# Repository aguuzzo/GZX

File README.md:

# **Robot Seguidor de Líneas**

Este proyecto implementa un robot seguidor de líneas basado en un Arduino Nano, 6 sensores CNY70, motores Pololu y un driver de motores. El robot utiliza un algoritmo de control para seguir de forma eficiente una línea negra sobre un fondo blanco.

---

## **Características**

- **Sensores:** 6 sensores CNY70 para detección precisa de la línea.  
- **Controlador:** Arduino Nano para procesamiento y control.  
- **Motores:** Motores Pololu de corriente continua para el movimiento.  
- **Driver de Motores:** Permite controlar la dirección y velocidad de los motores.  
- **Algoritmo de Control:** Basado en control proporcional (P) o proporcional-derivativo (PD) para seguir la línea.

---

## **Componentes**

- **Microcontrolador:** Arduino Nano (ATmega328P).  
- **Sensores:** 6 sensores ópticos CNY70.  
- **Motores:** Motores Pololu con caja reductora.  
- **Driver de Motores:** L298N o TB6612FNG.  
- **Fuente de Alimentación:** Batería de 7.4V (para los motores) y regulador de 5V para el Arduino y sensores.  
- **Estructura:** Chasis con diseño ligero y estable.  

---

## **Conexiones**

### **Sensores CNY70**  
Conectados a las entradas analógicas del Arduino:  
- **A0, A1, A2, A3, A4, A5.**  

### **Driver de Motores**  
Pines del Arduino conectados al driver:  
- **ENA:** Pin 9 (Control de velocidad motor izquierdo).  
- **IN1, IN2:** Pines 7 y 6 (Control dirección motor izquierdo).  
- **ENB:** Pin 10 (Control de velocidad motor derecho).  
- **IN3, IN4:** Pines 5 y 4 (Control dirección motor derecho).  

---

## **Algoritmo Implementado**

1. Leer los valores de los sensores (valores analógicos).  
2. Convertir los valores a binarios según un umbral.  
3. Calcular la posición de la línea en relación con el centro de los sensores.  
4. Determinar el error y ajustar la velocidad de los motores mediante un controlador proporcional (P).  
5. Enviar comandos al driver para mover los motores.

---

## **Prueba y ajustes**
1. Calibrar Sensores: Ajusta el umbral para detectar correctamente la línea.
2. Optimización del Controlador: Ajusta la constante proporcional Kp para evitar oscilaciones y mejorar la estabilidad.
3. Pruebas Dinámicas: Evalúa el rendimiento en distintas trayectorias (curvas, bifurcaciones, etc.).

## **Código**

### **Ejemplo: Controlador Proporcional**
```cpp
#include <Arduino.h>

// Pines de sensores
const int sensores[6] = {A0, A1, A2, A3, A4, A5};

// Pines del driver
const int ENA = 9; // Velocidad motor izquierdo
const int IN1 = 7;
const int IN2 = 6;
const int ENB = 10; // Velocidad motor derecho
const int IN3 = 5;
const int IN4 = 4;

int lecturaSensores[6];
int posicion = 0;
int error = 0;
int velocidadBase = 150;
float Kp = 10; // Constante proporcional

void setup() {
  for (int i = 0; i < 6; i++) pinMode(sensores[i], INPUT);
  pinMode(ENA, OUTPUT);
  pinMode(ENB, OUTPUT);
  pinMode(IN1, OUTPUT);
  pinMode(IN2, OUTPUT);
  pinMode(IN3, OUTPUT);
  pinMode(IN4, OUTPUT);
}

void loop() {
  // Leer sensores
  posicion = 0;
  for (int i = 0; i < 6; i++) {
    lecturaSensores[i] = analogRead(sensores[i]) > 500 ? 1 : 0; // Umbral 500
    posicion += lecturaSensores[i] * (i - 2); // Peso relativo de cada sensor
  }

  // Calcular error
  error = posicion;

  // Control proporcional
  int ajuste = Kp * error;

  // Calcular velocidades
  int velocidadIzquierda = velocidadBase - ajuste;
  int velocidadDerecha = velocidadBase + ajuste;

  // Controlar motores
  moverMotor(ENA, IN1, IN2, velocidadIzquierda);
  moverMotor(ENB, IN3, IN4, velocidadDerecha);
  delay(10);
}

void moverMotor(int enable, int in1, int in2, int velocidad) {
  if (velocidad > 0) {
    digitalWrite(in1, HIGH);
    digitalWrite(in2, LOW);
  } else {
    digitalWrite(in1, LOW);
    digitalWrite(in2, HIGH);
    velocidad = -velocidad;
  }
  analogWrite(enable, constrain(velocidad, 0, 255));
}

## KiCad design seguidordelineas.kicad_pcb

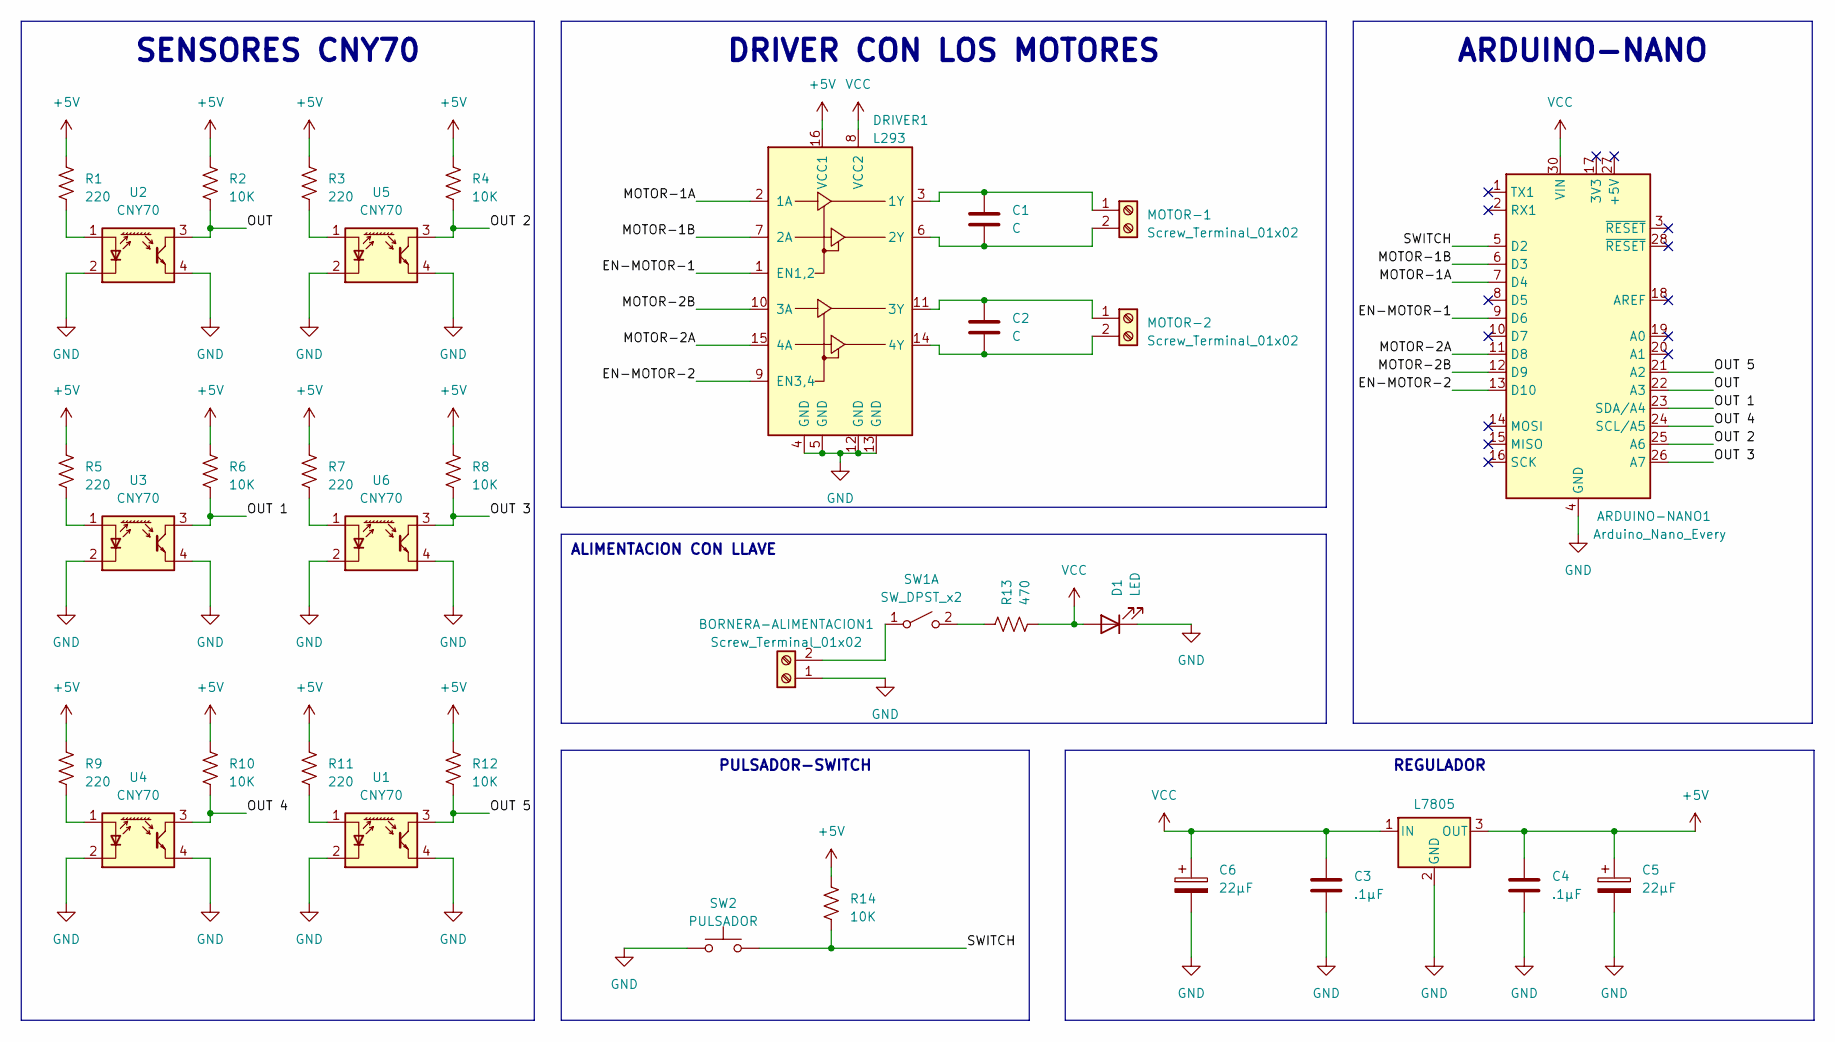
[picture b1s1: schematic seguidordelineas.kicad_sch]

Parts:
ARDUINO-NANO1: Arduino_Nano_Every; Arduino_Nano
BORNERA-ALIMENTACION1: Screw_Terminal_01x02; TerminalBlock_bornier-2_P5.08mm
C1, C2: C; CP_Radial_Tantal_D4.5mm_P2.50mm
C3, C4: .1μF; CP_Radial_Tantal_D4.5mm_P2.50mm
C5, C6: 22μF; CP_Radial_D5.0mm_P2.00mm
D1: LED; LED_D3.0mm_IRGrey
DRIVER1: L293; DIP-16_W7.62mm
MOTOR-1, MOTOR-2: Screw_Terminal_01x02; TerminalBlock_bornier-2_P5.08mm
R1, R3, R5, R7, R9, R11: 220; R_Axial_DIN0204_L3.6mm_D1.6mm_P7.62mm_Horizontal
R2, R4, R6, R8, R10, R12, R14: 10K; R_Axial_DIN0204_L3.6mm_D1.6mm_P7.62mm_Horizontal
R13: 470; R_Axial_DIN0204_L3.6mm_D1.6mm_P7.62mm_Horizontal
REGULADOR1: L7805; TO-220-3_Vertical
SW1: SW_DPST_x2; TerminalBlock_bornier-3_P5.08mm
SW2: PULSADOR; SW_PUSH_6mm_H4.3mm
U1, U2, U3, U4, U5, U6: CNY70; Vishay_CNY70

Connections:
+5V: C4.2, C5.1, DRIVER1.16 (VCC1), R1.1, R2.1, R3.1, R4.1, R5.1, R6.1, R7.1, R8.1, R9.1, R10.1, R11.1, R12.1, R14.1, REGULADOR1.3 (OUT)
/EN-MOTOR-1: ARDUINO-NANO1.9 (D6), DRIVER1.1 (EN1,2)
/EN-MOTOR-2: ARDUINO-NANO1.13 (D10), DRIVER1.9 (EN3,4)
/MOTOR-1A: ARDUINO-NANO1.7 (D4), DRIVER1.2 (1A)
/MOTOR-1B: ARDUINO-NANO1.6 (D3), DRIVER1.7 (2A)
/MOTOR-2A: ARDUINO-NANO1.11 (D8), DRIVER1.15 (4A)
/MOTOR-2B: ARDUINO-NANO1.12 (D9), DRIVER1.10 (3A)
/OUT: ARDUINO-NANO1.22 (A3), R2.2, U2.3 (C)
/OUT 1: ARDUINO-NANO1.23 (SDA/A4), R6.2, U3.3 (C)
/OUT 2: ARDUINO-NANO1.25 (A6), R4.2, U5.3 (C)
/OUT 3: ARDUINO-NANO1.26 (A7), R8.2, U6.3 (C)
/OUT 4: ARDUINO-NANO1.24 (SCL/A5), R10.2, U4.3 (C)
/OUT 5: ARDUINO-NANO1.21 (A2), R12.2, U1.3 (C)
/SWITCH: ARDUINO-NANO1.5 (D2), R14.2, SW2.2
GND: ARDUINO-NANO1.4 (GND), ARDUINO-NANO1.29 (GND), BORNERA-ALIMENTACION1.1, C3.2, C4.1, C5.2, C6.2, D1.1 (K), DRIVER1.4 (GND), DRIVER1.5 (GND), DRIVER1.12 (GND), DRIVER1.13 (GND), REGULADOR1.2 (GND), SW2.1, U1.2 (K), U1.4 (E), U2.2 (K), U2.4 (E), U3.2 (K), U3.4 (E), U4.2 (K), U4.4 (E), U5.2 (K), U5.4 (E), U6.2 (K), U6.4 (E)
unnamed: BORNERA-ALIMENTACION1.2, SW1.1 (A)
unnamed: C1.1, DRIVER1.3 (1Y), MOTOR-1.1
unnamed: C1.2, DRIVER1.6 (2Y), MOTOR-1.2
unnamed: C2.1, DRIVER1.11 (3Y), MOTOR-2.1
unnamed: C2.2, DRIVER1.14 (4Y), MOTOR-2.2
unnamed: R13.1, SW1.2 (B)
unnamed: R11.2, U1.1 (A)
unnamed: R1.2, U2.1 (A)
unnamed: R5.2, U3.1 (A)
unnamed: R9.2, U4.1 (A)
unnamed: R3.2, U5.1 (A)
unnamed: R7.2, U6.1 (A)
VCC: ARDUINO-NANO1.30 (VIN), C3.1, C6.1, D1.2 (A), DRIVER1.8 (VCC2), R13.2, REGULADOR1.1 (IN)

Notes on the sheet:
DRIVER CON LOS MOTORES
ALIMENTACION CON LLAVE
PULSADOR-SWITCH
REGULADOR
ARDUINO-NANO
SENSORES CNY70

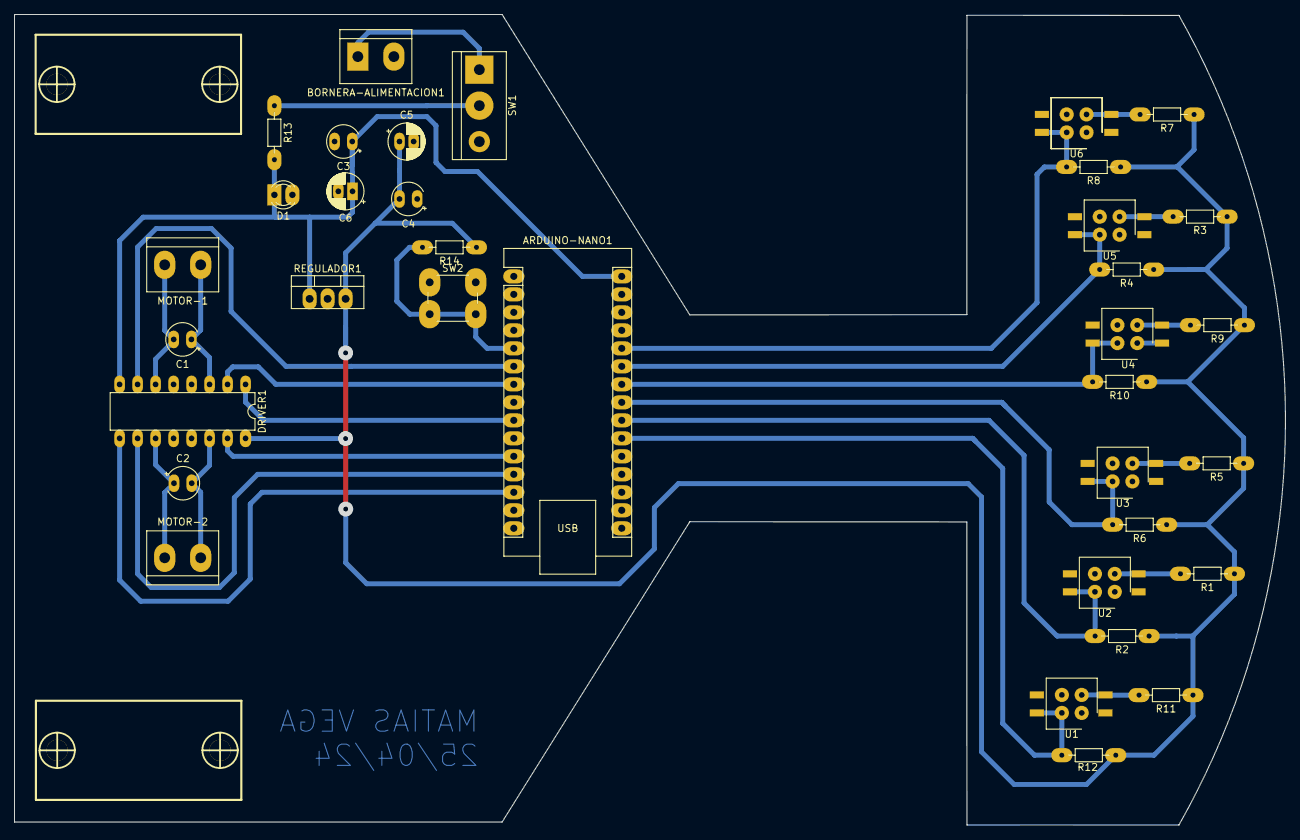
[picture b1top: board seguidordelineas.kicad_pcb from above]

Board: 2 copper layers, 179.4 x 114.4 mm, 37 parts (0 on the bottom side), 28 nets.

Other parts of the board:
Pololu_Micro_Gear_Motor: VAL**; Pololu_Micro_Con_Soporte_Simple
Pololu_Micro_Gear_Motor#2: VAL**; Pololu_Micro_Con_Soporte_Simple

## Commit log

2024-11-20 GZX9
